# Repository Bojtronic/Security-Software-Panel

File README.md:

# 🔐 Sistema de Control de Acceso -- Panel Electrónico Integrado

## 📌 Descripción del Proyecto

Este proyecto consiste en la **modernización e integración de un sistema
de control de acceso** basado en panel eléctrico, actualmente compuesto
por múltiples módulos independientes.

La nueva solución propone el diseño de una **tarjeta electrónica (PCB)
unificada**, que centraliza el control del sistema mediante un
microcontrolador **ESP32**, mejorando la mantenibilidad, escalabilidad y
facilidad de configuración.

------------------------------------------------------------------------

## 🎯 Objetivos

-   Integrar múltiples módulos en una sola tarjeta electrónica
-   Simplificar el mantenimiento del sistema
-   Permitir configuración remota (sin abrir el panel)
-   Mantener la funcionalidad del sistema actual
-   Mejorar la confiabilidad y orden del sistema

------------------------------------------------------------------------

## ⚙️ Sistema Actual

### 🔧 Componentes

-   Sensores de proximidad
-   Módulos de relés independientes
-   Fuente de poder
-   Batería de 12V
-   Temporizador / reloj
-   Receptor inalámbrico + control remoto
-   Cerraduras magnéticas

### 🔄 Funcionamiento

-   Al detectar una persona, se desbloquea la puerta
-   Si no se abre en 5 segundos, se vuelve a bloquear
-   Si se abre, se bloquea al cerrarse nuevamente
-   Horario de funcionamiento: **9:00 AM -- 5:00 PM**
    -   Dentro del horario: entrada y salida permitidas
    -   Fuera del horario: solo salida permitida
-   Control remoto permite:
    -   Bloquear puertas
    -   Liberar puertas
    -   Enviar señal de emergencia

------------------------------------------------------------------------

## 🚀 Nueva Solución Propuesta

### 🧠 Arquitectura

El sistema será rediseñado utilizando:

-   🧩 **PCB diseñada en KiCad**
-   ⚡ **Microcontrolador ESP32**
-   🔌 Alimentación de **12V DC**
-   🔋 Sistema de respaldo con batería
-   🔁 Sistema de carga automática de batería

------------------------------------------------------------------------

## 🔌 Entradas y Salidas

### 📥 Entradas

-   2 × Sensores de proximidad (contacto seco)
-   3 × Señales de control remoto:
    -   Bloquear
    -   Liberar
    -   Emergencia

### 📤 Salidas

-   4 × Relés:
    -   Control de cerradura (bloqueo/desbloqueo)
    -   Señal de emergencia (luz externa)
    -   Señal a centro de monitoreo
    -   Salida adicional configurable

------------------------------------------------------------------------

## 🔄 Lógica de Funcionamiento

El nuevo sistema mantiene la lógica actual:

-   Detección de persona → desbloqueo de puerta
-   Temporizador de 5 segundos si no se abre
-   Bloqueo automático al cerrar la puerta
-   Restricción por horario:
    -   Dentro del horario: acceso completo
    -   Fuera del horario: solo salida

------------------------------------------------------------------------

## 🎮 Control Remoto

### Funcionalidades requeridas:

-   🔒 Bloqueo total (anula sensores) (C)
-   🔓 Liberación total (anula sensores) (A)
-   🚨 Señal de emergencia: (B-D) ambos
    -   Activación de luz externa
    -   Notificación al centro de monitoreo

> ⚠️ Se evaluará una alternativa más moderna al sistema actual de
> control remoto y receptor inalámbrico.

------------------------------------------------------------------------

## 🔋 Sistema de Energía

-   Alimentación principal: **12V DC**
-   Batería de respaldo:
    -   Se activa automáticamente ante fallo eléctrico
-   Carga de batería:
    -   Automática cuando hay alimentación AC
    -   Protección contra sobrecarga

------------------------------------------------------------------------

## 💻 Configuración y Mantenimiento

-   Configuración del sistema mediante **ESP32**
-   Acceso desde laptop (posibles opciones):
    -   Interfaz web
    -   Conexión serial / USB
    -   WiFi

### Parámetros configurables:

-   Horario de funcionamiento
-   Tiempos de desbloqueo
-   Estados de relés
-   Configuración de entradas/salidas

------------------------------------------------------------------------

## 🛠️ Herramientas de Desarrollo

-   🧩 **KiCad** -- Diseño de PCB
-   💻 **Arduino IDE** -- Programación del ESP32
-   📝 **Visual Studio Code** -- Edición de código y control de
    versiones

------------------------------------------------------------------------

## 📈 Mejoras Clave

-   Integración total del hardware en una sola PCB
-   Reducción de cableado y puntos de falla
-   Configuración sin abrir el panel
-   Mayor claridad para mantenimiento técnico
-   Escalabilidad futura

------------------------------------------------------------------------

## 🧪 Estado del Proyecto

🚧 En desarrollo

-   [x] Definición de requerimientos
-   [ ] Diseño esquemático en KiCad
-   [ ] Diseño de PCB
-   [ ] Desarrollo de firmware ESP32
-   [ ] Pruebas funcionales
-   [ ] Implementación en campo

------------------------------------------------------------------------

## 🔮 Posibles Mejoras Futuras

-   Aplicación web para monitoreo en tiempo real
-   Registro de eventos (logs)
-   Integración con sistemas de seguridad centralizados
-   Notificaciones remotas
-   Uso de tecnologías IoT

------------------------------------------------------------------------

## 📄 Licencia

Este proyecto es de uso interno / privado.

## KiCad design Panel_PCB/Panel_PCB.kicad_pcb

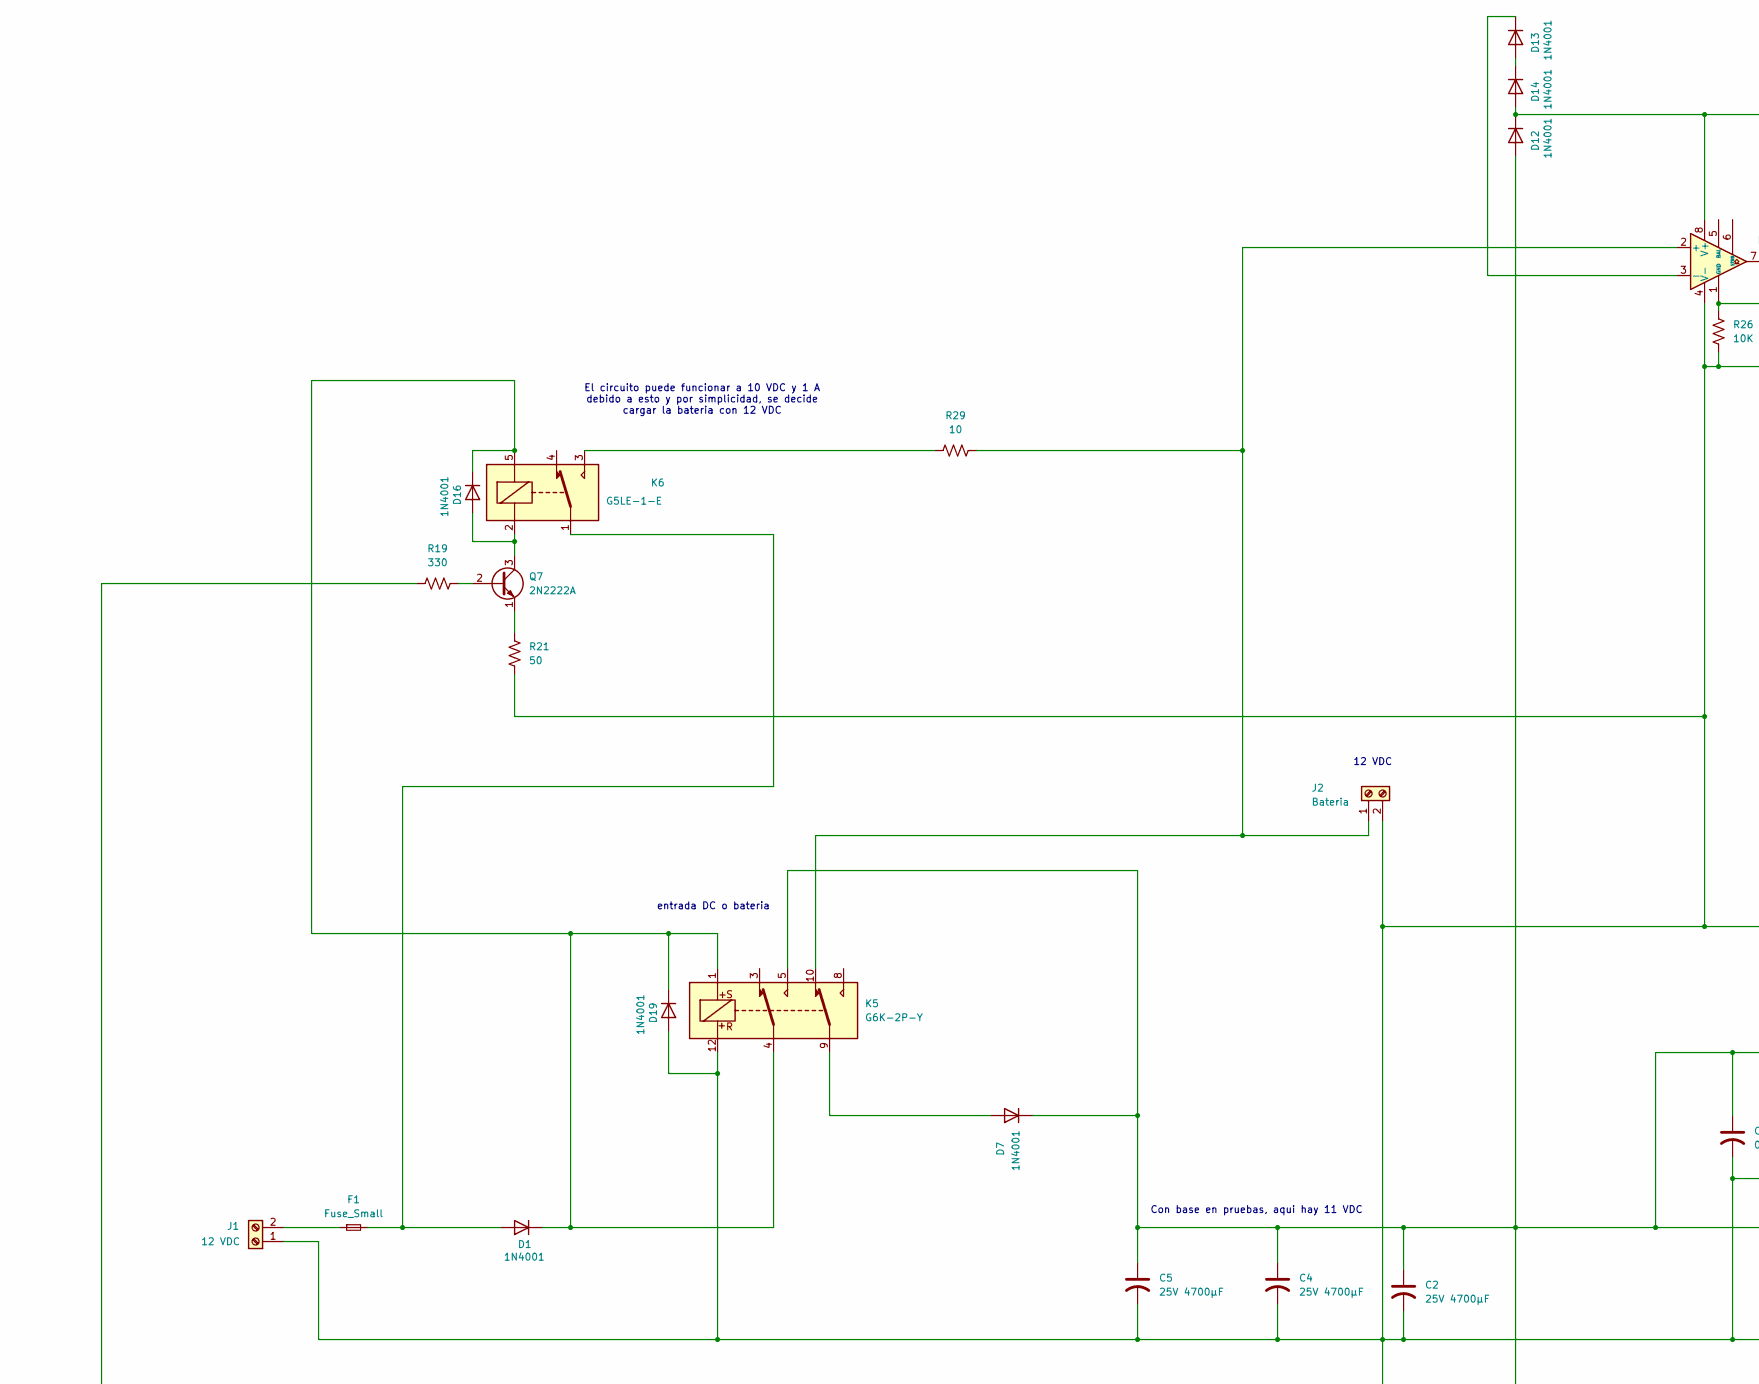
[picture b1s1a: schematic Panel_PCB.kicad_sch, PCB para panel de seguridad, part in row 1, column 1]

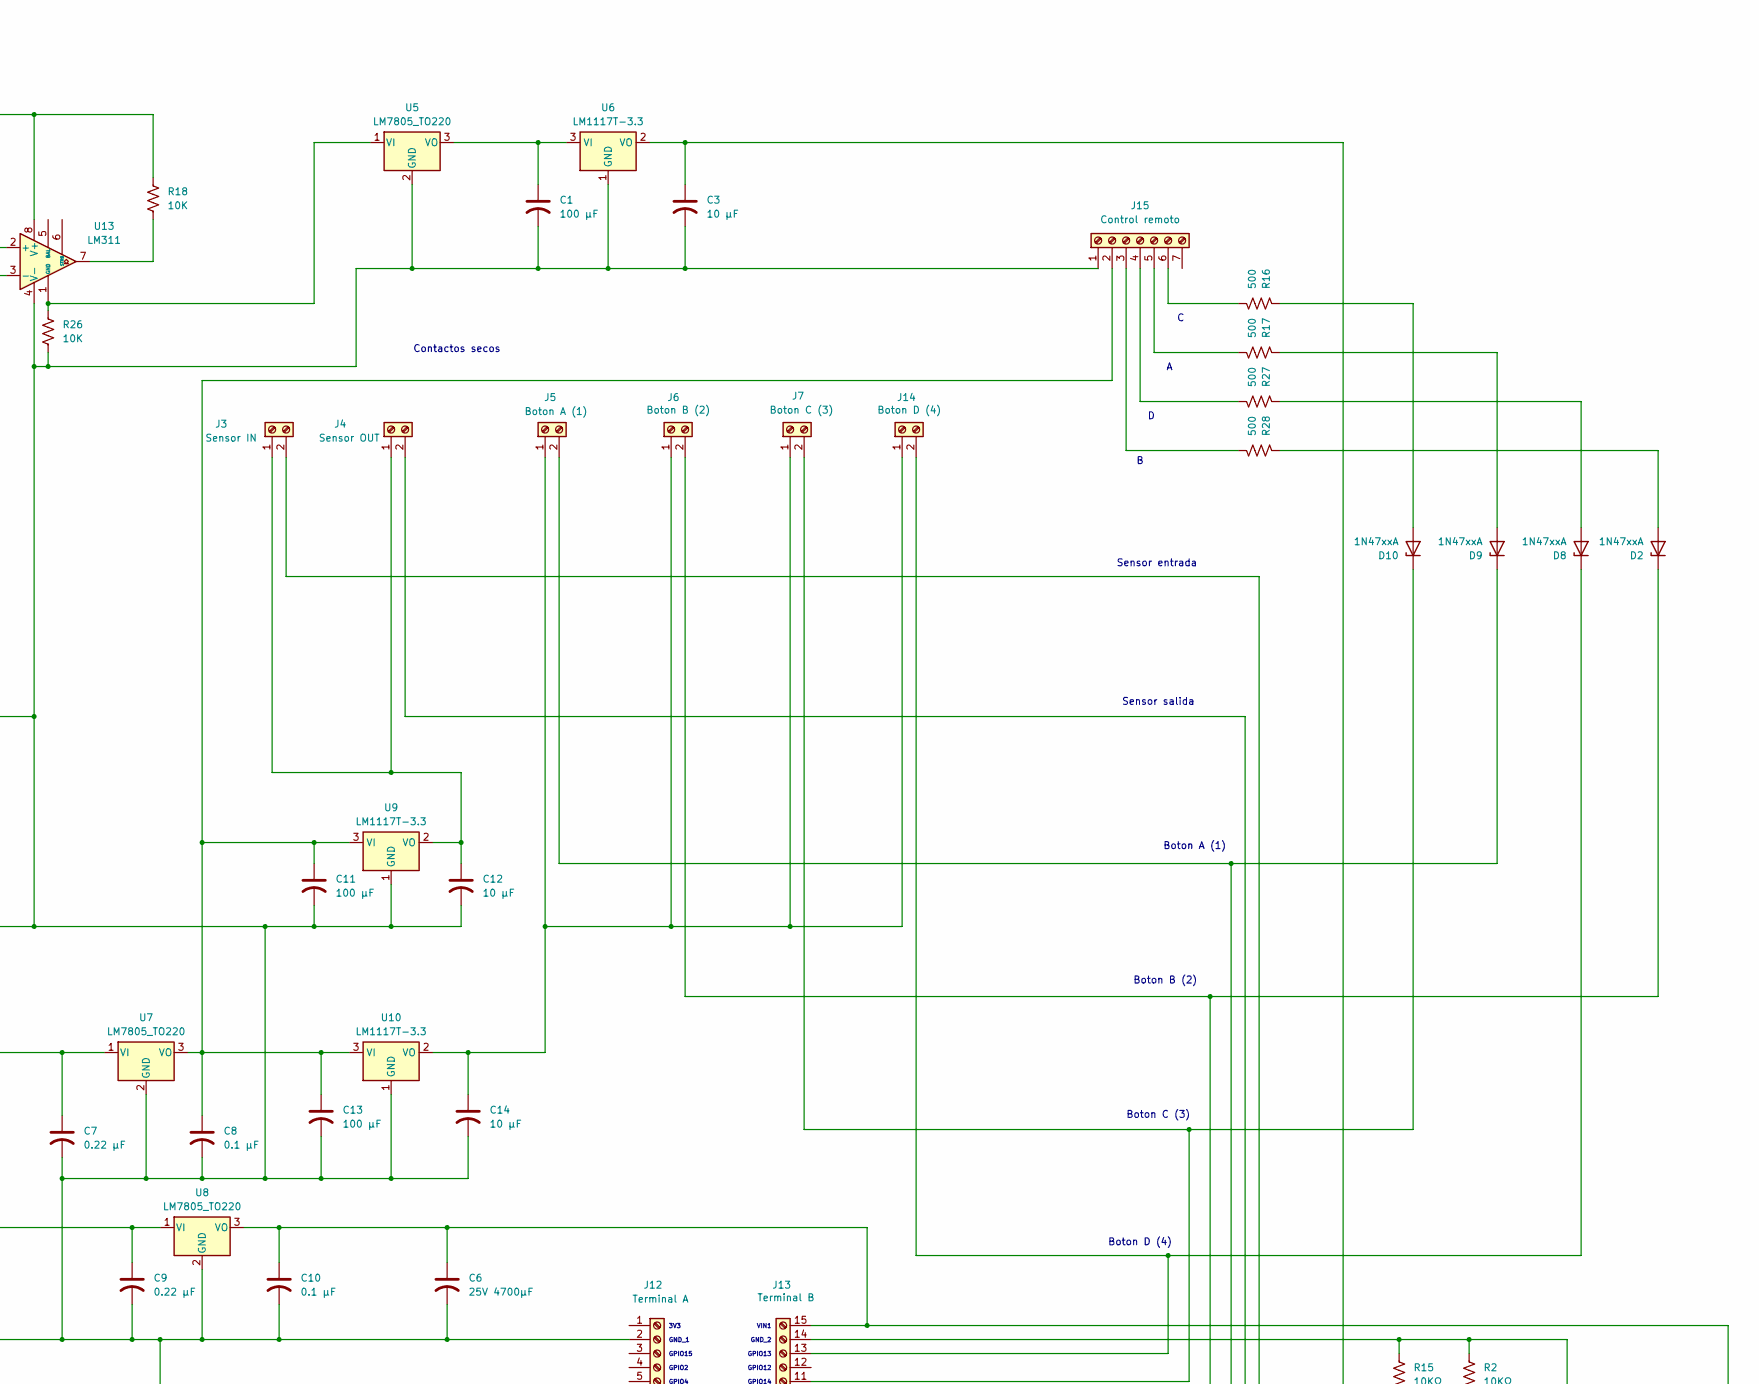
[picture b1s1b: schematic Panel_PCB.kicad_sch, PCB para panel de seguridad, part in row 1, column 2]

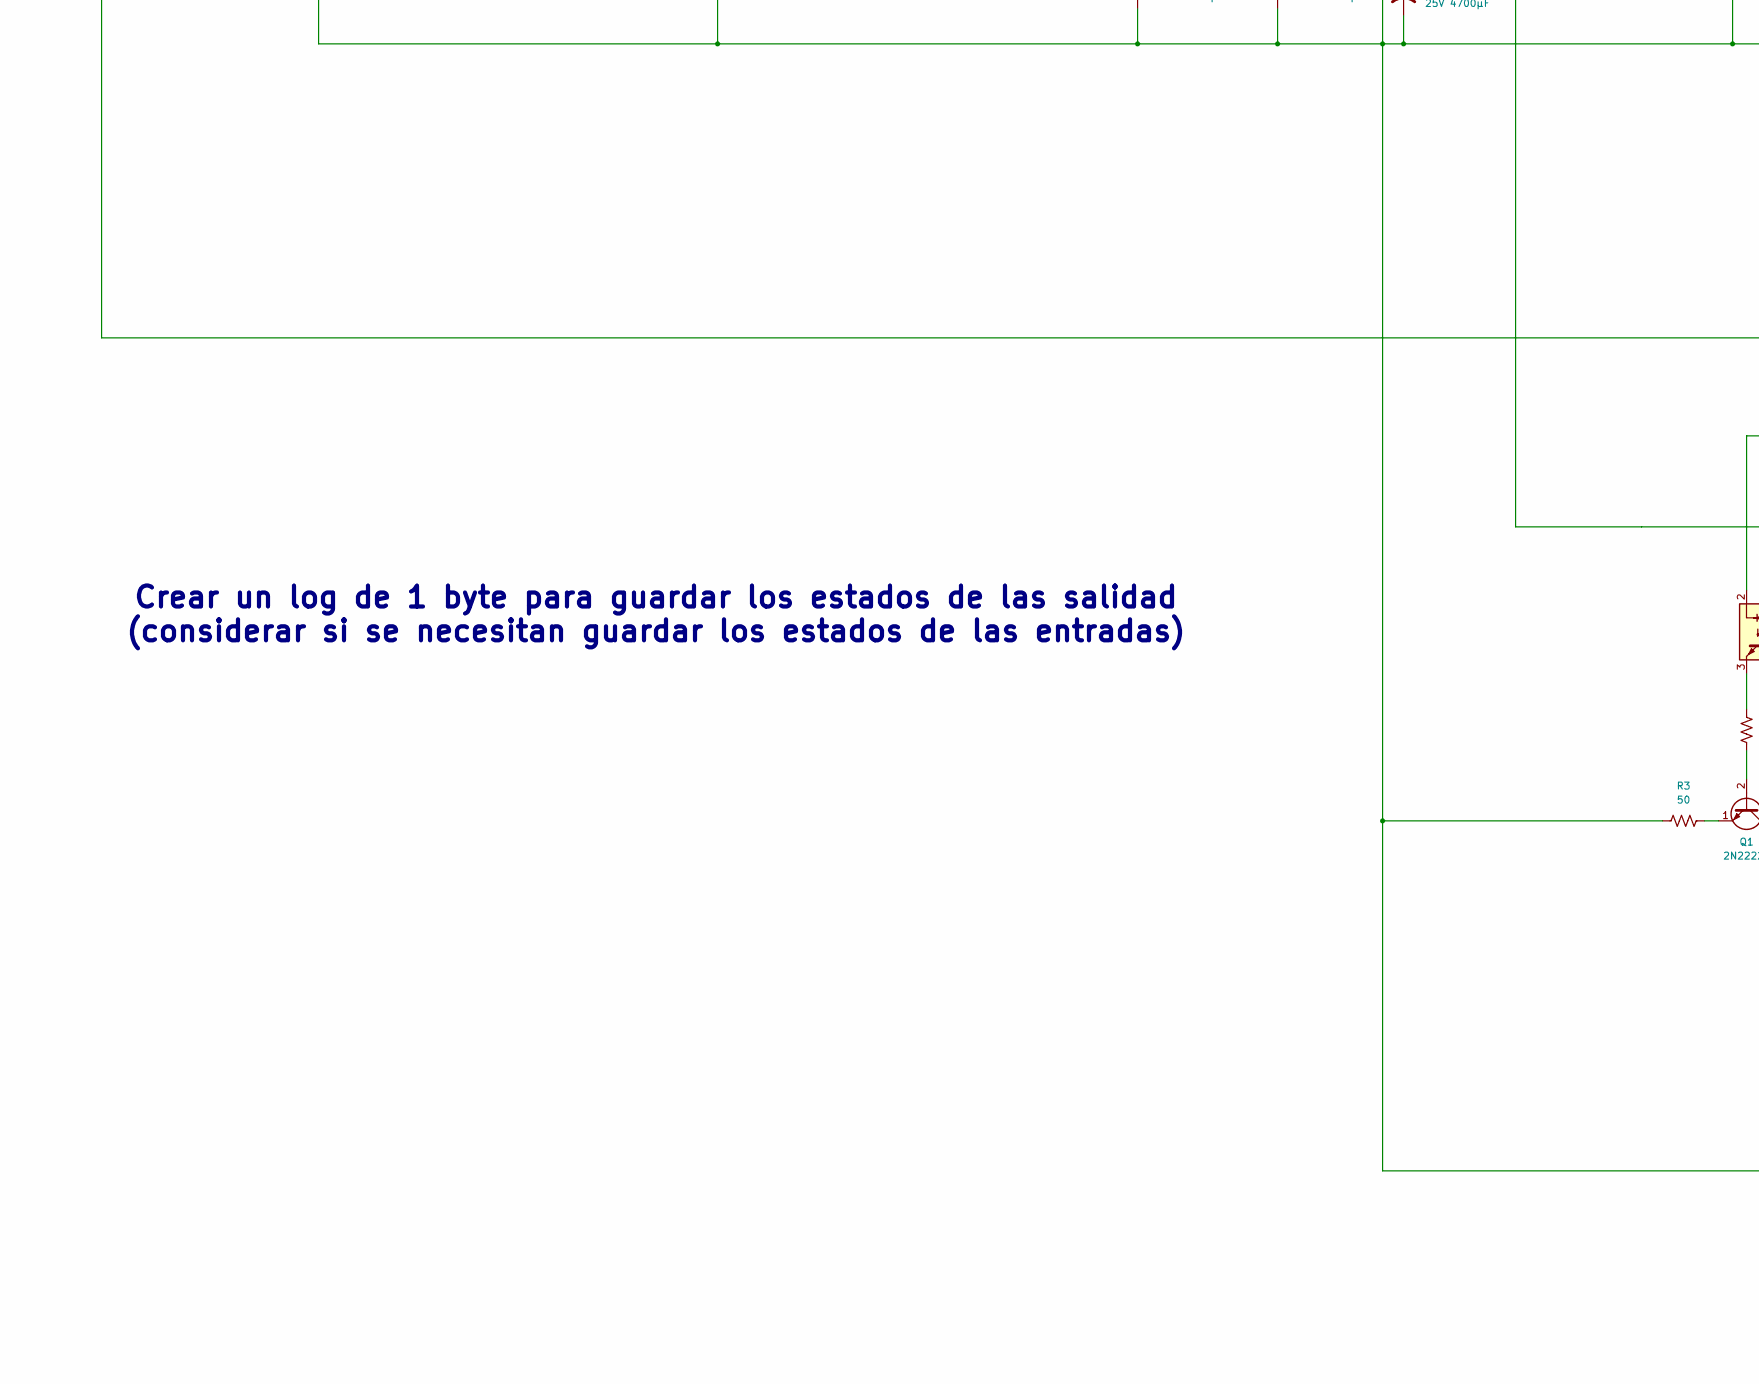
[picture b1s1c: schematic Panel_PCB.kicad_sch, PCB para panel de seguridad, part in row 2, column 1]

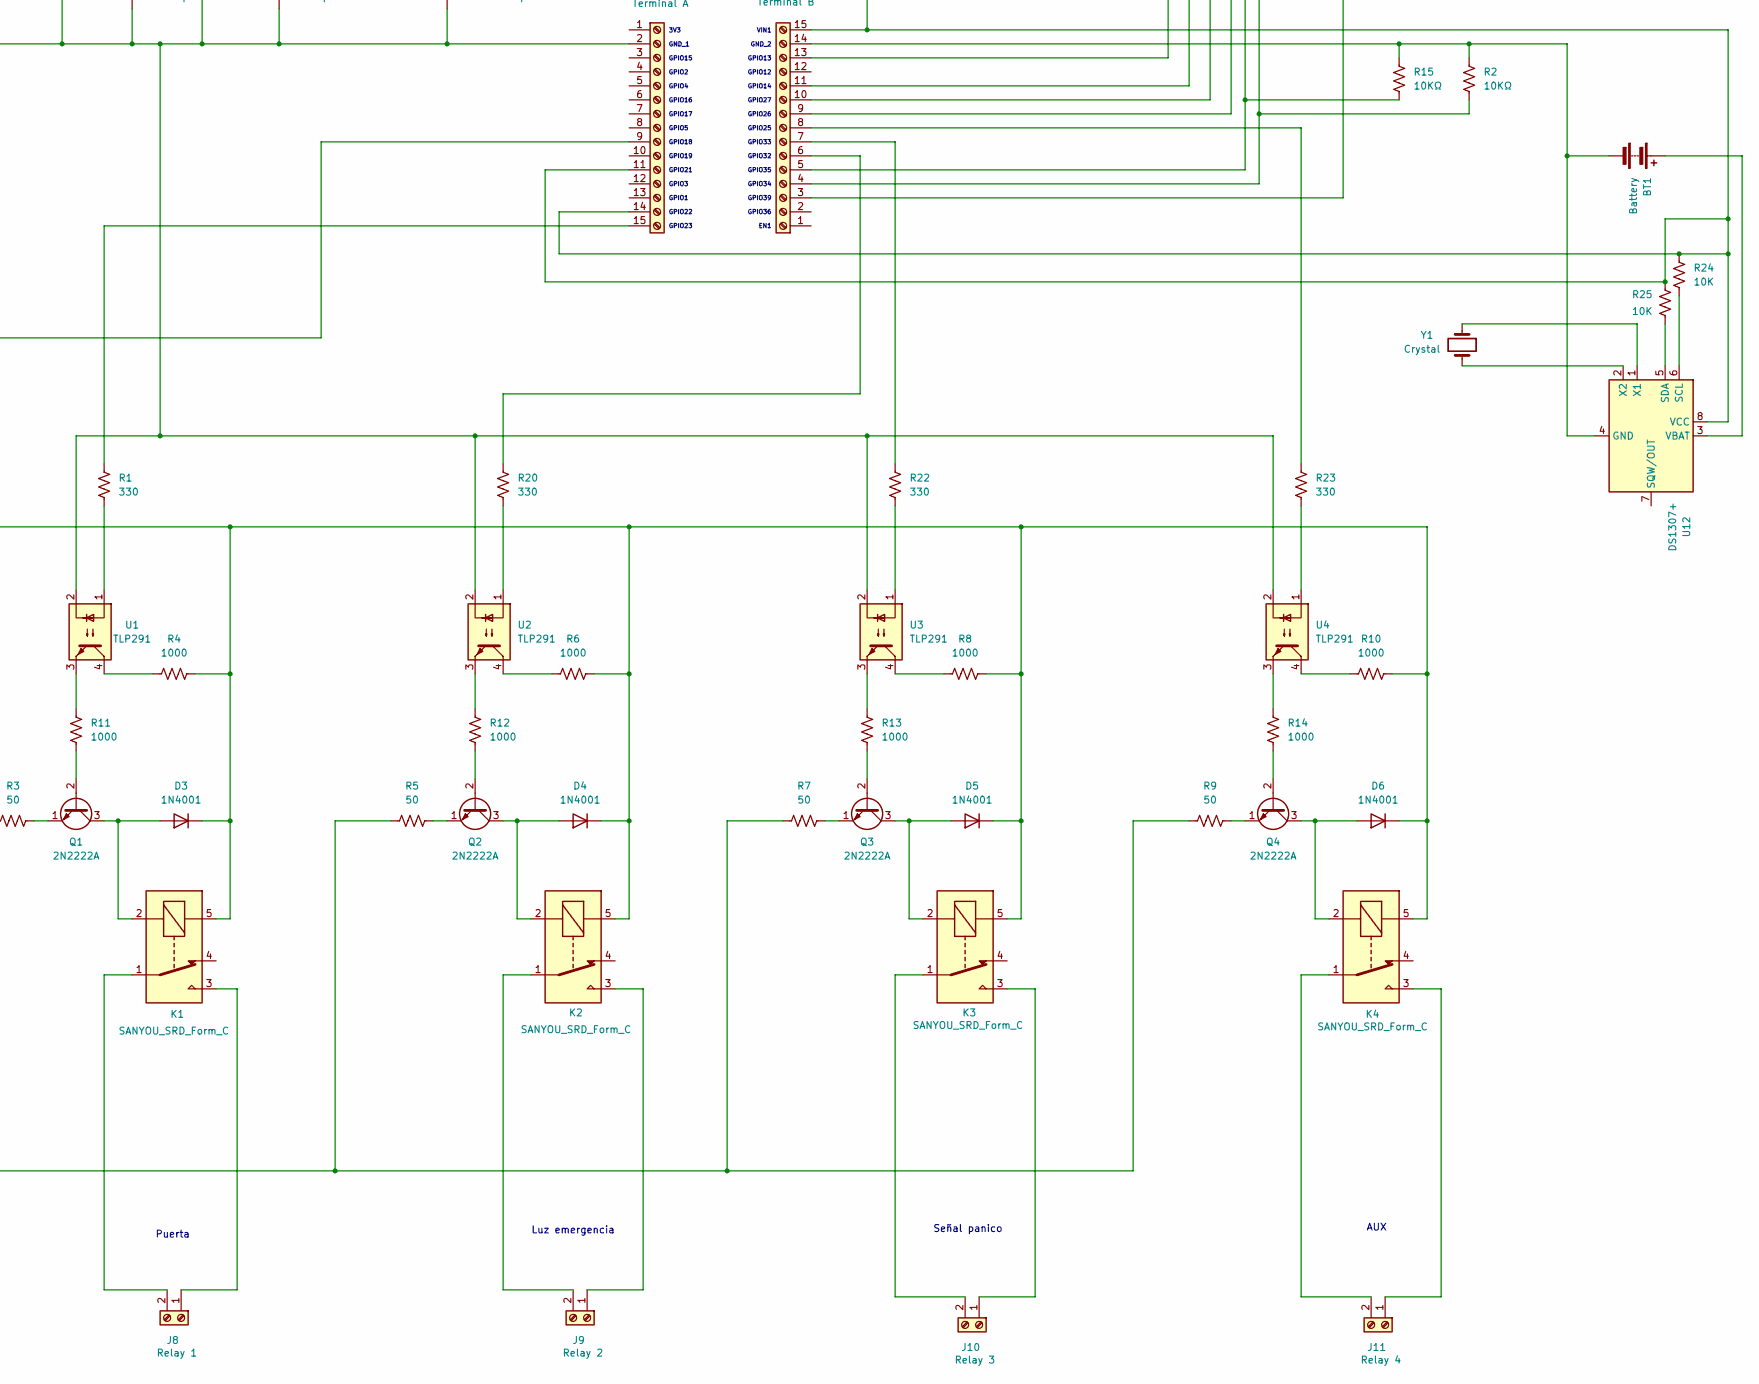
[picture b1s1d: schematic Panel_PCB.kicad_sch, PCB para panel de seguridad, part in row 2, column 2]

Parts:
BT1: Battery; BatteryHolder_Keystone_1060_1x2032
C1, C11, C13: 100 μF; C_Disc_D3.0mm_W1.6mm_P2.50mm
C2, C4, C5, C6: 25V 4700μF; C_Radial_D18.0mm_H35.5mm_P7.50mm
C3, C12, C14: 10 μF; C_Disc_D3.0mm_W1.6mm_P2.50mm
C7, C9: 0.22 μF; C_Disc_D3.0mm_W1.6mm_P2.50mm
C8, C10: 0.1 μF; C_Disc_D3.0mm_W1.6mm_P2.50mm
D1, D3, D4, D5, D6, D7, D12, D13, D14, D16, D19: 1N4001; D_DO-41_SOD81_P10.16mm_Horizontal
D2, D8, D9, D10: 1N47xxA; D_DO-41_SOD81_P10.16mm_Horizontal
F1: Fuse_Small; Fuseholder_Cylinder-5x20mm_Schurter_0031_8201_Horizontal_Op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
J1: 12 VDC; TerminalBlock_Phoenix_MKDS-1,5-2-5.08_1x02_P5.08mm_Horizont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
J2: Bateria; TerminalBlock_Phoenix_MKDS-1,5-2-5.08_1x02_P5.08mm_Horizont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
J3: Sensor IN; TerminalBlock_Phoenix_MKDS-1,5-2-5.08_1x02_P5.08mm_Horizont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
J4: Sensor OUT; TerminalBlock_Phoenix_MKDS-1,5-2-5.08_1x02_P5.08mm_Horizont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
J5: Boton A (1); TerminalBlock_Phoenix_MKDS-1,5-2-5.08_1x02_P5.08mm_Horizont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
J6: Boton B (2); TerminalBlock_Phoenix_MKDS-1,5-2-5.08_1x02_P5.08mm_Horizont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
J7: Boton C (3); TerminalBlock_Phoenix_MKDS-1,5-2-5.08_1x02_P5.08mm_Horizont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
J8: Relay 1; TerminalBlock_Phoenix_MKDS-1,5-2-5.08_1x02_P5.08mm_Horizont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
J9: Relay 2; TerminalBlock_Phoenix_MKDS-1,5-2-5.08_1x02_P5.08mm_Horizont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
J10: Relay 3; TerminalBlock_Phoenix_MKDS-1,5-2-5.08_1x02_P5.08mm_Horizont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
J11: Relay 4; TerminalBlock_Phoenix_MKDS-1,5-2-5.08_1x02_P5.08mm_Horizont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
J12: Terminal A; TerminalBlock_Xinya_XY308-2.54-15P_1x15_P2.54mm_Horizontal
J13: Terminal B; TerminalBlock_Xinya_XY308-2.54-15P_1x15_P2.54mm_Horizontal
J14: Boton D (4); TerminalBlock_Phoenix_MKDS-1,5-2-5.08_1x02_P5.08mm_Horizont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
J15: Control remoto; TerminalBlock_Xinya_XY308-2.54-7P_1x07_P2.54mm_Horizontal
K1, K2, K3, K4: SANYOU_SRD_Form_C; Relay_SPDT_SANYOU_SRD_Series_Form_C
K5: G6K-2P-Y; Relay_DPDT_Kemet_EC2_NU
K6: G5LE-1-E; Relay_SPDT_Omron-G5LE-1
Q1, Q2, Q3, Q4, Q7: 2N2222A; TO-92
R1, R20, R22, R23: 330; R_Axial_DIN0207_L6.3mm_D2.5mm_P10.16mm_Horizontal
R2, R15: 10KΩ; R_Axial_DIN0207_L6.3mm_D2.5mm_P10.16mm_Horizontal
R3, R5, R7, R9, R21: 50; R_Axial_DIN0309_L9.0mm_D3.2mm_P12.70mm_Horizontal
R4, R6, R8, R10, R11, R12, R13, R14: 1000; R_Axial_DIN0207_L6.3mm_D2.5mm_P10.16mm_Horizontal
R16, R17, R27, R28: 500; R_Axial_DIN0207_L6.3mm_D2.5mm_P10.16mm_Horizontal
R18, R26: 10K; R_Axial_DIN0309_L9.0mm_D3.2mm_P12.70mm_Horizontal
R19: 330; R_Axial_DIN0309_L9.0mm_D3.2mm_P12.70mm_Horizontal
R24, R25: 10K; R_Axial_DIN0207_L6.3mm_D2.5mm_P10.16mm_Horizontal
R29: 10; R_Axial_Power_L60.0mm_W14.0mm_P66.04mm
U1, U2, U3, U4: TLP291; DIP-4_W7.62mm
U5, U7, U8: LM7805_TO220; TO-220-3_Vertical
U6, U9, U10: LM1117T-3.3; TO-220-3_Vertical
U12: DS1307+; DIP-8_W7.62mm
U13: LM311; DIP-8_W7.62mm
Y1: Crystal; Crystal_C26-LF_D2.1mm_L6.5mm_Horizontal

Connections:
unnamed: BT1.1 (+), U12.3 (VBAT)
unnamed: BT1.2 (-), J13.14, R2.1, R15.1, U12.4 (GND)
unnamed: D1.2 (A), F1.2, K6.1
unnamed: D1.1 (K), D16.1 (K), D19.1 (K), K5.1, K5.4, K6.5
unnamed: D2.2 (A), R28.2
unnamed: D2.1 (K), J6.2, J13.10
unnamed: D3.2 (A), K1.2, Q1.3 (C)
unnamed: D4.2 (A), K2.2, Q2.3 (C)
unnamed: D5.2 (A), K3.2, Q3.3 (C)
unnamed: D6.2 (A), K4.2, Q4.3 (C)
unnamed: D7.2 (A), K5.9
unnamed: D8.2 (A), R27.2
unnamed: D8.1 (K), J13.13, J14.2
unnamed: D9.2 (A), R17.2
unnamed: D9.1 (K), J5.2, J13.9
unnamed: D10.2 (A), R16.2
unnamed: D10.1 (K), J7.2, J13.11
unnamed: C2.1, C4.1, C5.1, C7.1, C9.1, D3.1 (K), D4.1 (K), D5.1 (K), D6.1 (K), D7.1 (K), D12.2 (A), K1.5, K2.5, K3.5, K4.5, K5.5, R4.1, R6.1, R8.1, R10.1, U7.1 (VI), U8.1 (VI)
unnamed: D12.1 (K), D14.2 (A), R18.1, U13.8 (V+)
unnamed: D13.2 (A), D14.1 (K)
unnamed: D13.1 (K), U13.3 (-)
unnamed: D16.2 (A), K6.2, Q7.3 (C)
unnamed: C1.2, C2.2, C3.2, C4.2, C5.2, C6.2, C7.2, C8.2, C9.2, C10.2, C11.2, C12.2, C13.2, C14.2, D19.2 (A), J1.1, J2.2, J12.2, J15.1, K5.12, R3.2, R5.2, R7.2, R9.2, R21.2, R26.2, U1.2, U2.2, U3.2, U4.2, U5.2 (GND), U6.1 (GND), U7.2 (GND), U8.2 (GND), U9.1 (GND), U10.1 (GND), U13.4 (V-)
unnamed: F1.1, J1.2
unnamed: J2.1, K5.10, R29.2, U13.2 (+)
unnamed: C12.1, J3.1, J4.1, U9.2 (VO)
unnamed: J8.1, K1.3
unnamed: J8.2, K1.1
unnamed: J9.1, K2.3
unnamed: J9.2, K2.1
unnamed: J10.1, K3.3
unnamed: J10.2, K3.1
unnamed: J11.1, K4.3
unnamed: J11.2, K4.1
unnamed: J12.9, R19.2
unnamed: C6.1, C10.1, J12.11, J12.14, J13.15, R24.1, R25.2, U8.3 (VO), U12.8 (VCC)
unnamed: J12.15, R1.1
unnamed: C3.1, J13.3, U6.2 (VO)
unnamed: J3.2, J13.4, R2.2
unnamed: J4.2, J13.5, R15.2
unnamed: J13.6, R20.1
unnamed: J13.7, R22.1
unnamed: J13.8, R23.1
unnamed: C14.1, J5.1, J6.1, J7.1, J14.1, U10.2 (VO)
unnamed: C8.1, C11.1, C13.1, J15.2, U7.3 (VO), U9.3 (VI), U10.3 (VI)
unnamed: J15.3, R28.1
unnamed: J15.4, R27.1
unnamed: J15.5, R17.1
unnamed: J15.6, R16.1
unnamed: K6.3, R29.1
unnamed: Q1.2 (B), R11.1
unnamed: Q1.1 (E), R3.1
unnamed: Q2.2 (B), R12.2
unnamed: Q2.1 (E), R5.1
unnamed: Q3.2 (B), R13.2
unnamed: Q3.1 (E), R7.1
unnamed: Q4.2 (B), R14.2
unnamed: Q4.1 (E), R9.1
unnamed: Q7.2 (B), R19.1
unnamed: Q7.1 (E), R21.1
unnamed: R1.2, U1.1
unnamed: R4.2, U1.4
unnamed: R6.2, U2.4
unnamed: R8.2, U3.4
unnamed: R10.2, U4.4
unnamed: R11.2, U1.3
unnamed: R12.1, U2.3
unnamed: R13.1, U3.3
unnamed: R14.1, U4.3
unnamed: R18.2, U13.7
unnamed: R20.2, U2.1
unnamed: R22.2, U3.1
unnamed: R23.2, U4.1
unnamed: C1.1, U5.3 (VO), U6.3 (VI)
unnamed: R24.2, U12.6 (SCL)
unnamed: R25.1, U12.5 (SDA)
unnamed: U12.1 (X1), Y1.1
unnamed: U12.2 (X2), Y1.2
unnamed: R26.1, U5.1 (VI), U13.1 (GND)

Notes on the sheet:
Sensor entrada
Luz emergencia
Puerta
Boton A (1)
Señal panico
El circuito puede funcionar a 10 VDC y 1 A debido a esto y por simplicidad, se decide cargar la bateria con 12 VDC
Con base en pruebas, aqui hay 11 VDC
VIN1 GND_2 GPIO13 GPIO12 GPIO14 GPIO27 GPIO26 GPIO25 GPIO33 GPIO32 GPIO35 GPIO34 GPIO39 GPIO36 EN1
Boton B (2)
Boton C (3)
entrada DC o bateria
AUX
3V3 GND_1 GPIO15 GPIO2 GPIO4 GPIO16 GPIO17 GPIO5 GPIO18 GPIO19 GPIO21 GPIO3 GPIO1 GPIO22 GPIO23
Boton D (4)
Sensor salida
Crear un log de 1 byte para guardar los estados de las salidad (considerar si se necesitan guardar los estados de las entradas)
Contactos secos
12 VDC

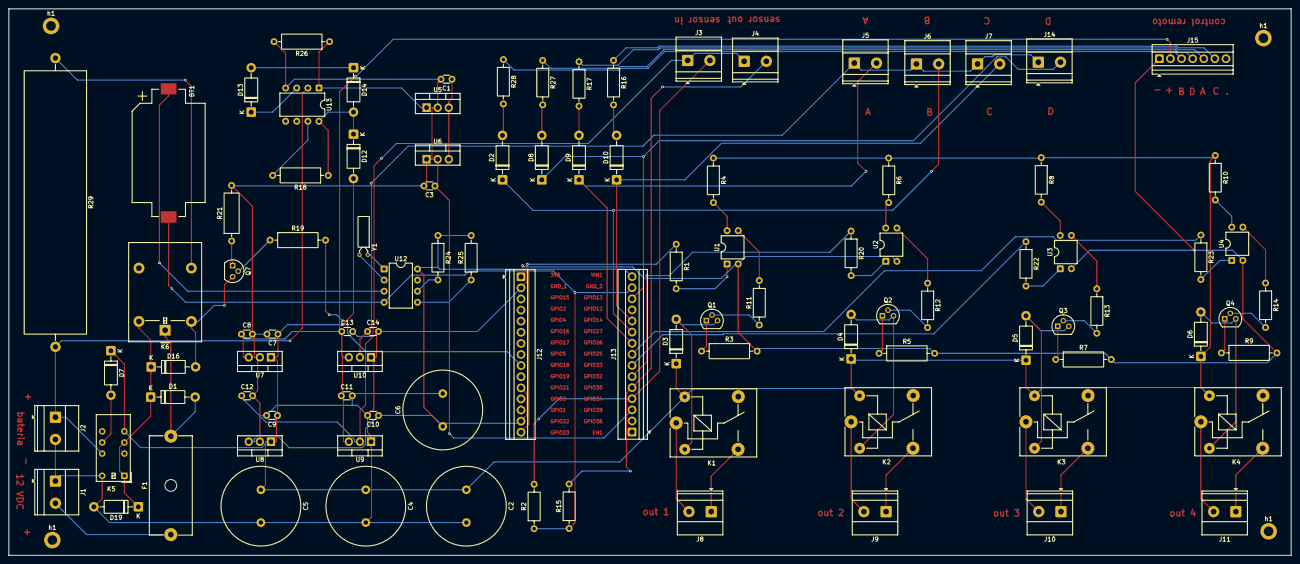
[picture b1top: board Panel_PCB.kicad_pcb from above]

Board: 2 copper layers, 293.3 x 125.0 mm, 103 parts (0 on the bottom side), 79 nets.

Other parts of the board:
h1, h1#2, h1#3, h1#4: MountingHole_2.2mm_M2_DIN965_Pad

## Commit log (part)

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2025-11-24 Inicio del proyecto en KiCad
2025-11-25 Imagenes y layout para el esp32 en la placa
2025-11-25 Layout para el esp32 en la placa
2025-12-02 Simulación para activación de pines y paro de emergencia
2025-12-05 Recursos útiles para el diseño electrónico
2026-01-07 Organización de elementos
2026-01-09 Conexiones, componentes y recursos
2026-01-10 Analisis del sistema actual y planteamiento para la nueva solucion
2026-01-12 Esquema semi-definitivo (faltan conexiones y analisis)
2026-02-02 Conexiones para activar reles
2026-02-03 Huellas y valores a componentes
2026-02-04 Corrección de errores
2026-02-04 Organizando elementos del PCB
2026-02-04 Estructura general del codigo
2026-02-04 Actualización del código
2026-02-14 Conexiones al microcontrolador
2026-02-20 Actualización de PCB
2026-02-20 Circuitos para detectar bateria descargada y circuito para cargar la batería
2026-03-04 Analisis de circuitos para detección de voltaje y carga de bateria
2026-03-25 DS1307 y bateria para mantener la hora actualizada
2026-03-27 Comparador de voltaje (para el cargador de batería)
2026-03-28 Cambiar alimentación a 12 VDC
2026-03-28 Nuevo esquematico (falta boost converter de 12V a 13.5V
2026-03-30 Ajustes al esquemático
2026-03-30 Actualización de placa
2026-04-02 Actualización de esquematico
2026-04-06 Entradas (sensores y botones). Salidas (relés)
2026-04-08 Archivo readme
2026-04-10 Update README.md
    Agregue información hacia los botones del inalámbrico.
2026-04-10 Actualización
2026-04-10 Update README.md
    Corrección de descripción de los nombres en las funciones del control remoto.
2026-04-19 Actualización del esquema y el software
2026-04-19 Actualización del software
2026-04-26 Corrección a las entradas
2026-05-02 Cambios al codigo
2026-05-02 Actualización de esquematico: resistencias de pulldown a los pines de los sensores
2026-05-09 Monitoreo de la carga de la batería
2026-05-24 Información para usar el control remoto
2026-06-15 Ajuste al esquematico
